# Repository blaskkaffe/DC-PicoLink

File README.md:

# DC-PicoLink

> **Part of the DC- Dreamcast family** (branch `unified`): [DC-DreamDash](https://github.com/blaskkaffe/DC-DreamDash/tree/unified) · [DC-PicoLink](https://github.com/blaskkaffe/DC-PicoLink/tree/unified) · [DC-iBlueControlMod](https://github.com/blaskkaffe/DC-iBlueControlMod/tree/unified) · [DC-BlueRetro](https://github.com/blaskkaffe/DC-BlueRetro/tree/unified) · [DC-openMenu-Virtual-Folder-Bundle](https://github.com/blaskkaffe/DC-openMenu-Virtual-Folder-Bundle/tree/unified) · [DC-Pico2Maple](https://github.com/blaskkaffe/DC-Pico2Maple/tree/unified). They work alone and together. The shared plan, feature list, vocabulary and licenses overview are in [docs/unified/](docs/unified/README.md).

> ⚠️ **Under development. No guarantee that anything here works.**
> Use it at your own risk, on hardware you can afford to lose: wiring mistakes or firmware
> bugs can damage a Dreamcast, a modem or the boards. Tried on hardware: the RP2040 cable with
> DreamPi, and the **RP2040-Zero + ESP32-S3 SuperMini stack** on a breadboard (the boards joined
> by wires) over the serial cable: Wi-Fi, PPP, DNS, VPN, UPnP, DCNow!; Quake, Quake III, Unreal
> Tournament, Alien Front Online. Written and host-tested but **not tried on hardware yet**: the
> soldered stack, the SD slot and its files over Wi-Fi, W5500 emulation through the ESP32, the
> BBA port, the USB modem, DCNet, Netlink. Expect bugs; the checklist is
> [docs/TESTING.md](docs/TESTING.md). When you report a problem, include the first status line
> (firmware version) and the log.

An RP2040-based Dreamcast serial-port adapter: a full coder's cable (serial and serial
PPP), W5500 Ethernet emulation over USB networking, and SD card emulation (used by
openMenu for its settings and VMU backups). Works with DreamPi or a regular computer,
as a cheaper, faster alternative to separate coder's cables and W5500 adapters, and (being
built) with an ESP32-S3 instead of a computer: [hardware/ESP32.md](hardware/ESP32.md), [esp32/](esp32).

One small board on the Dreamcast's serial port shows up on the computer as one USB
device with three functions. It works out by itself which one the Dreamcast is using:

| The Dreamcast thinks it has… | Used for | On the computer |
|---|---|---|
| a **coder's cable** (UART) | dc-tool-ser / dcload-serial, the KOS console, serial PPP games (e.g. AFO through DreamPi's Netlink) | a USB serial port (`/dev/dccable` on DreamPi) |
| a **WIZnet W5500** Ethernet chip | KallistiOS homebrew and patched games with the W5500 driver | a USB network interface (`dcusb0`) the computer routes or bridges |
| an **SD card** | openMenu (settings, per-game VMU backups), other SCIF-SPI SD programs | a disk image on the host (DreamPi), or a microSD in the board's own slot (written, not tried on hardware); with the ESP32, the slot card's files over Wi-Fi |

## Status

Working on hardware with DreamPi (Raspberry Pi, Linux):

* Serial: dc-tool-ser / dcload-serial 1.0.6 uploads clean at 115200 and 1.5 Mbaud
  (1.6 Mbaud is above what the Dreamcast's SCIF can do), the KOS console, Netlink serial
  PPP. Exact Dreamcast baud rates and auto-baud. No flow control from the Dreamcast, as
  DreamPi 2.1 (games and current KallistiOS leave its RTS floating, and waiting for it
  blocked the cable: DEVLOG, Nov 2026).
* W5500: KOS networking, DreamKarts and RuneScape online, JaderFox tester, ping, Quake 3
  server list and play (with `dcusb0-masterfix`).
* Being tested: AFO over serial (drops while fetching game info), Quake 3 map images over
  serial, Unreal Tournament (needs its server's address), Dreamcast Now! for W5500.
* SD card: works with KOS's SD driver; openMenu 1.7.1 doesn't find the card yet.

On a DreamPi the W5500 Dreamcast is meant to look exactly like DreamPi's modem Dreamcast
(DreamPi is the reference; its behaviour is written down in the project's DreamPi spec):

| | DreamPi add-on (`host/dreampi`) |
|---|---|
| Dreamcast Live VPN address (T+1) | `dcusb0-vpn` |
| Own LAN address (DreamPi's, e.g. .98): Internet traffic, router port forwards | `LAN_ALIAS=auto` |
| DreamPi's DNS (community DNS + DreamPi's overrides) | `DNS=auto` |
| TTL 64, PowerSmash double-SYN filter | `dcusb0-vpn` / DreamPi's own rule |
| DreamPi's game packet helpers (dcgamespy, dc2k2, dcvoip, dcdaytona) | fed / kept correct for `dcusb0` |
| Dreamcast Now! "online" | `dcusb0-dcnow` |
| Quake 3 server list (master ignores the word `dreamcast`) | `dcusb0-masterfix` (ours) |

The ESP32 (no computer) applies the same rules itself; what is still missing is listed in
[hardware/ESP32.md](hardware/ESP32.md) and the project's DreamPi spec. Tried over the serial cable
on a breadboard build (see the warning at the top).

Other hosts (Linux PC, macOS, Windows, Android) are planned: see [docs/ROADMAP.md](docs/ROADMAP.md).

## The stack: RP2040-Zero + ESP32-S3 SuperMini (no computer needed)

Tried on a breadboard build over the serial cable; the soldered stack is next. The two boards
sit back to back; the RP2040 does everything towards the Dreamcast, the ESP32 the Internet
side. Pinout: [Wiring](#wiring-full-pinout) below, details in [hardware/ESP32.md](hardware/ESP32.md);
ESP32 details: [esp32/README.md](esp32/README.md).

| | What it does | Like DreamPi |
|---|---|---|
| Internet | home Wi-Fi, or a W5500 Ethernet module on the ESP32 as uplink | |
| Setup | own Wi-Fi network `DC-PicoLink-XXXX`, web page with status, log, settings | |
| Serial cable | modem emulation (`AT`, `ATD`), PPP server, NAT | serial PPP |
| W5500 emulation | the Dreamcast's W5500 network: DHCP, DNS, NAT | `dcusb0` |
| SD card | a microSD on the Zero's SPI1 is the Dreamcast's SD card | (dcsd image) |
| SD files | the slot card's files on the web page: copy saves to and from a computer or phone | |
| USB modem | a USB voice modem on the ESP32: dial tone, number, answer, PPP | yes |
| BBA | the Dreamcast's Broadband Adapter on the ESP32's W5500 module | |
| DNS | DreamPi's DNS list from dreamcast.online, revival DNS; over TCP when the router intercepts DNS | yes |
| DCNow! | reports, and `dreampi.local:1998` for dreamcast.online/now/configure | yes |
| Network switch | two buttons at the top of the page: DCNow! (default) or DCNet, from the next call, whatever number the game dials; `*69` still goes to DCNet while DCNow! is selected (tick box). Also `call net.select dcnow\|dcnet` in the DC API (`POST /dcapi`), `POST /dcnow`, `/dcnet`, `GET /tag`, `/openmenu/poll` | yes |
| Wi-Fi from the console | `call wifi.scan`, `get wifi.scan.*`, `set wifi.pass ...`, `call wifi.join <name or #n>` in the DC API, and the page's Search button (list, filter, tap to pick) | |
| DCNet | `*69` before the number, or every call (the switch) | yes |
| Netlink | direct dial, matchmaking, game server codes, XBAND, Capcom matching (USB modem) | yes |
| VPN | Dreamcast Live, profiles built in (okayed by Dreamcast Live); the Dreamcast gets its own VPN address; auto mode pings every server and takes the fastest | yes |
| Own home address | as DreamPi: the Dreamcast gets .98 on your network (this box .99, answers ARP for it, no NAT); 1:1 with the VPN up | yes |
| Port forwarding | DreamPi's game ports by UPnP straight to the Dreamcast's .98, nothing else; says when the provider shares your IPv4 (then the VPN is switched on) | yes (optional there) |
| Game packet rules | TTL 64, PowerSmash double SYN, Planet Ring / Daytona public address, DNAT address swaps (dnat.txt) | yes |
| Serial line queue | game (UDP) packets go ahead of downloads on the slow serial line | |
| Updates | both boards from the web page (ESP32 image; the Zero restarts into its USB drive) | |

Test before trusting it: [docs/TESTING.md](docs/TESTING.md).

## Wiring (full pinout)

The stack: an RP2040-Zero and an ESP32-S3 SuperMini, back to back. Every signal below is 3.3 V
logic. The older single-board layouts (a Pico or Pro Micro with the Dreamcast on GPIO2-7, a UART
link to the ESP32) are only for testing: [hardware/WIRING.md](hardware/WIRING.md). More detail:
[hardware/ESP32.md](hardware/ESP32.md), [hardware/SD-SLOT.md](hardware/SD-SLOT.md).

### Dreamcast side

The usual way in is a **DC SD Adapter V2** in the serial port with an SD extender / sniffer
board in its slot (the adapter only maps the port's pins to SD contacts). An internal install
solders the same signals to the serial port's pins. Names are the Dreamcast's own (its TXD is
what it sends).

| Dreamcast signal | Serial port pin | SD contact: full-size / microSD | RP2040-Zero | Needed for |
|---|---|---|---|---|
| TXD (SPI MOSI) | 5 | 2 CMD / 3 | GP10 | serial, W5500, SD |
| RXD (SPI MISO) | 4 | 7 DAT0 / 7 | GP11 | serial, W5500, SD |
| RTS (SPI CS) | 6 | 1 DAT3 / 2 | GP12 | W5500, SD (serial only reads it) |
| CTS (SPI clock) | 7 | 5 CLK / 5 | GP9 | W5500, SD (the cable reads the line) |
| CTS drive | – | – | GP13 **→ 1 kΩ →** GP9 | serial flow control; a resistor on the board, no wire to the Dreamcast |
| GND | 3, 8 | 3 + 6 VSS / 6 | GND | everything |
| 3.3 V sense (optional) | 10 | 4 VDD / 4 | GP29 **via 10 kΩ** (about 10 kΩ; 9.1 kΩ is fine) | knowing when the Dreamcast is on; never to the board's 3V3 |
| +5 V | 1 | – | not connected | see [Power](#power-and-usb) |

**Which wires are needed.** Serial alone works with TXD, RXD and GND. W5500 and the SD card use
all four signal wires (TXD, RXD, RTS, CTS), because there they are the SPI bus: so with all three
functions, wire all four. CTS is one pin on the Dreamcast that does two jobs. In serial mode it is
an input: the cable pulls it high through GP13 to say "stop sending" when its buffer is nearly
full. In W5500/SD mode the Dreamcast turns it into the SPI clock, an output. GP9 reads what is
really on the line (which is also how the cable notices SPI mode), and the 1 kΩ lets both sides
drive it without harm ([why](hardware/WIRING.md#why-the-1-kω-resistor)). Without the GP13
resistor serial still works, but the cable can no longer slow the Dreamcast down. The sense wire
is optional: without it the cable decides the Dreamcast is on when it sees TXD or RTS high.
Serial port pins 2 and 9 and SD contacts 8 and 9 (DAT1, DAT2) stay unconnected. The pin numbers come from coder's
cable guides: measure before soldering.

### The stack: which pins are joined

RP2040-Zero on top, face up; ESP32-S3 SuperMini underneath, face down; both USB sockets at
the same end; positions count from the USB end. **Solder only what the table says**, and put
insulation (Kapton) between the two boards' backs.

| Pos | Zero left ↔ SuperMini | | Zero right ↔ SuperMini | |
|---|---|---|---|---|
| 1 | 5V ↔ 5V | **solder** | GP0 ↔ GPIO43 | optional (ESP32 console TX) |
| 2 | GND ↔ GND | **solder** | GP1 ↔ GPIO44 | optional (ESP32 console RX) |
| 3 | 3V3 ↔ 3V3 | **never** (two regulators) | GP2 ↔ GPIO1 | not used (optional, strength) |
| 4 | GP29 ↔ GPIO13 | **never** (GP29 is the power sense / W5500 MISO) | GP3 ↔ GPIO2 | **solder**: HS (ESP32 ready) |
| 5 | GP28 ↔ GPIO12 | **never** (SD MISO / W5500 SCLK) | GP4 ↔ GPIO3 | **solder**: SPI MISO (ESP32 → Zero) |
| 6 | GP27 ↔ GPIO11 | **never** (GP27 free / W5500 MOSI) | GP5 ↔ GPIO4 | **solder**: SPI CS |
| 7 | GP26 ↔ GPIO10 | **never** (SD SCK / W5500 CS) | GP6 ↔ GPIO5 | **solder**: SPI clock |
| 8 | GP15 ↔ GPIO9 | **never** (SD MOSI / W5500 INT) | GP7 ↔ GPIO6 | **solder**: SPI MOSI (Zero → ESP32) |
| 9 | GP14 ↔ GPIO8 | **never** (GP14 is the SD card's CS) | GP8 ↔ GPIO7 | **solder**: DR (ESP32 has data) |

Left 4-9 are the Zero's power sense (GP29), SD slot pins (GP28, GP26, GP15, GP14) and the free GP27 over the ESP32's W5500 pins (GPIO9-13):
all used, each from the outside (the Zero's edge pads, the SuperMini's holes from its outer face), none joined.
The same pin map serves the stripboard layout ([hardware/STRIPBOARD.md](hardware/STRIPBOARD.md); a PCB with an SD-card plug: [hardware/stack-pcb](hardware/stack-pcb/README.md)): there the boards stand side by side. The Zero's bottom
edge GP9-13 is the Dreamcast (table above). GP16 is the Zero's own RGB LED (red: no ESP32,
yellow: damaged link packets, green: link up, blue: link up and the Dreamcast on).

### SD card slot (optional)

A 3.3 V microSD module or breakout on the RP2040-Zero's SPI1, never on the Dreamcast's wires.

| SD module | RP2040-Zero |
|---|---|
| CLK / SCK | GP26 |
| CMD / DI / MOSI | GP15 (Pico layout: GP27) |
| DAT0 / DO / MISO | GP28 |
| DAT3 / CS | GP14 |
| VCC / GND | 3V3 or 5V, see [SD-SLOT.md](hardware/SD-SLOT.md#which-vcc) / GND |

No card-detect pin: the cable looks for a card every 2 s.

### ESP32-S3 extras (optional)

| ESP32-S3 SuperMini | Connects to |
|---|---|
| GPIO12 | W5500 module SCLK |
| GPIO11 | W5500 module MOSI |
| GPIO13 | W5500 module MISO |
| GPIO10 | W5500 module CS (SCS) |
| GPIO9 | W5500 module INT |
| 3V3, GND | W5500 module 3.3 V, GND |
| USB-C (modem build) | a USB host for one device (a hub works too): a USB voice modem through an OTG adapter (the Dreamcast's modem joins it by a phone cord, as with a DreamPi), or a DC-PicoLink cable: the link then runs over USB, no link wires needed |
| GPIO43 / GPIO44 | console TX / RX (UART0, 115200) |

The W5500 module is the Internet uplink when a router answers DHCP on it, otherwise the
socket for the Dreamcast's Broadband Adapter.

### Power and USB

* **Today:** 5V and GND are joined, so either board's USB powers both. **Plug in one USB at a
  time** (the Zero has no diode on its USB 5 V). The Zero's USB is for updates and for a
  computer (it then takes the serial and network traffic, as with DreamPi); the ESP32's USB-C
  is its console, or in the modem build the socket for a USB modem, a USB Ethernet adapter or a
  DC-PicoLink cable (then the link runs over USB and needs no link wires; the ESP32 powers it).
* **From the Dreamcast (serial port pin 1, +5 V):** not measured yet, so not recommended. Any
  such feed goes through a Schottky diode (e.g. SS14) so a USB cable plugged in later can't push
  power back into the console. Current budget and options: [hardware/ESP32.md](hardware/ESP32.md#power).
* Never join the Dreamcast's 3.3 V (port pin 10 / SD VDD) to a board's 3V3: it goes only to the
  sense pin, through 10 kΩ.

## IP plan

The same Dreamcast settings work on the ESP32 box and on a DreamPi with this add-on. 98: the
Dreamcast's launch year in Japan, and its usual last number on the home network.

| Network | The box (or Pi) | The Dreamcast |
|---|---|---|
| Setup Wi-Fi `DC-PicoLink-XXXX` (ESP32) | 192.168.4.1: the web page (also `http://dreampi.local`) | – |
| **The Dreamcast network**: the W5500 (cable), the BBA socket (W5500 module), a PPP call without its home address | 192.168.98.1: gateway and DNS | DHCP .2–.99 (a PPP call gets .2); a fixed address at **.100** or above, mask 255.255.255.0, gateway and DNS 192.168.98.1 |
| Modem / serial PPP with its home address (default) | home network, usually .99 | home network, usually .98 (no NAT; port forwarding points there). Picked as DreamPi does: counting down from .99, the first free address is the box's end of the link, the next the Dreamcast's |
| VPN (Dreamcast Live) | the address the server gives | that address + 1 (only the server's game networks go through the tunnel) |
| DreamPi's W5500 network (`dcusb0`) | 192.168.98.1 | DHCP .10–.50, fixed .100 or above |

The Dreamcast uses one way to connect at a time, so they share one network: the box answers on
the interface the Dreamcast was last heard on. On the W5500, gateway and DNS must be set to
192.168.98.1 (0.0.0.0 only works over the modem, where PPP fills them in).

Which address where (the ESP32 box):

| Dreamcast joined by | Internet over | The Dreamcast gets |
|---|---|---|
| The cable's emulated W5500 (RP2040) | Wi-Fi or the wired uplink | 192.168.98.x (DHCP), NAT to the uplink |
| BBA into the W5500 module (BBA role) | Wi-Fi only: the module's one port is the Dreamcast's | 192.168.98.x (DHCP), NAT to Wi-Fi |
| Modem (USB) or the cable's serial port | Wi-Fi or the wired uplink | home network .98 (or 192.168.98.2 when no home address is free) |

The W5500 module picks its role by itself: if a router answers DHCP on its cable it is the way to
the Internet (the router's address, ahead of Wi-Fi), if nothing answers in 10 s it is the BBA
socket. A USB Ethernet adapter is not supported yet.

## Quick start (DreamPi)

1. **Wire it** to the Dreamcast serial port: [hardware/WIRING.md](hardware/WIRING.md)
   (SD-adapter plug build; an internal install works the same way).
2. **Flash** a Raspberry Pi Pico: hold BOOTSEL, plug in, copy
   `dc-picolink-<version>-250mhz.uf2` from the [releases](../../releases).
3. **Install the DreamPi side**: copy `dc-picolink-dreampi-setup.sh` to the Pi and run
   `sudo bash dc-picolink-dreampi-setup.sh`.
4. **Serial PPP** (Netlink): in DreamPi's `netlink_config.ini` set `port = /dev/dccable`.
5. **W5500**: the Dreamcast gets an address by DHCP (192.168.98.x). Static settings:
   IP 192.168.98.100, mask 255.255.255.0, gateway 192.168.98.1, DNS 192.168.98.1 (DreamPi's DNS;
   46.101.91.123 without DreamPi). Settings: `/etc/dcusb0.conf` (an untouched 192.168.99.x one from
   an older version is replaced by the installer with 192.168.98.x).
6. **Check**: `sudo dreampi-snapshot` prints what the DreamPi and the add-on are doing.

Logs: `journalctl -fu dcsd` (the cable's own status lines), `journalctl -u dcusb0`,
`journalctl -u dcusb0-vpn`, `journalctl -u dcusb0-dcnow`, `journalctl -u dcusb0-masterfix`.

dcload test: build dc-tool-ser on the Pi (KallistiOS `dcload-serial`, `make -C host-src/tool`),
boot a dcload-serial CDI, then `dc-tool-ser -t /dev/dccable -b 1500000 -x program.elf`.

## Repository

| Folder | |
|---|---|
| [`firmware/`](firmware) | RP2040 firmware (Pico SDK, PIO) and its host-side tests (`firmware/tests`) |
| [`host/`](host) | software for the computer side: `dreampi/` today; `linux/`, `macos/`, `windows/` planned |
| [`esp32/`](esp32) | ESP32-S3 firmware: the cable's link to Wi-Fi without a computer (under test) |
| [`hardware/`](hardware) | wiring and build notes, [SD slot](hardware/SD-SLOT.md), [ESP32](hardware/ESP32.md) |
| [`docs/`](docs) | [architecture](docs/ARCHITECTURE.md), [technical reference](docs/REFERENCE.md), [roadmap](docs/ROADMAP.md), [testing](docs/TESTING.md), [development log](docs/DEVLOG.md) |
| [`tools/`](tools) | test runner (`run-tests.sh`) and the scripts it calls, DreamPi installer builder, `dctest/` (Dreamcast test program and host tool), network-namespace tests of the DreamPi add-on, `dreampi_vpn_extract.py` (VPN profiles out of a DreamPi image, plain Python, works in a-Shell on iOS) |

## Building

Cable (RP2040), Pico SDK 2.1.1 and `gcc-arm-none-eabi`:

```sh
# Test layout, single Pico / Pro Micro (Dreamcast on GPIO2-7, ESP32 link on UART GPIO12-15)
cmake -S firmware -B build -DPICO_BOARD=pico -DDC_SYS_KHZ=250000 && make -C build
# The stack: RP2040-Zero + ESP32-S3 SuperMini (Dreamcast on GP9-14, ESP32 link over SPI)
cmake -S firmware -B build-zero -DPICO_BOARD=pico -DDC_SYS_KHZ=250000 -DDC_BOARD=zero-stack && make -C build-zero
```

The UF2 is `build*/dc_usb_serial.uf2`: hold BOOT (BOOTSEL), plug in, copy it to the drive.
`-DPICO_BOARD=pico` is right for the RP2040-Zero and Pro Micro too (generic 2 MB flash).

ESP32-S3, ESP-IDF 5.4 (details in [esp32/README.md](esp32/README.md)):

```sh
cd esp32
idf.py set-target esp32s3 && idf.py build                                             # UART link (test layout)
idf.py -B build-zero -D SDKCONFIG=build-zero/sdkconfig \
       -D SDKCONFIG_DEFAULTS="sdkconfig.defaults;sdkconfig.zero-stack" build          # SPI link (stack)
idf.py -B build-modem -D SDKCONFIG=build-modem/sdkconfig \
       -D SDKCONFIG_DEFAULTS="sdkconfig.defaults;sdkconfig.zero-stack;sdkconfig.modem" build   # + USB modem port
```

Tests (host, no hardware): `tools/run-tests.sh` runs the C model tests, including the SPI
link's timing simulation; `tools/run-tests.sh build` adds the PIO simulations for both
Dreamcast pin layouts. More options: [docs/REFERENCE.md#build](docs/REFERENCE.md#build).
CI builds every push; tagged versions (`v*`) become releases with the UF2 files and the
DreamPi installer.

Part of a family of `DC-` Dreamcast projects.

`esp32/probe` is a test firmware for one question: can the ESP32-S3 do the RP2040's job too?
Measured: no (Wi-Fi pauses the other core for ~40 ns). See [hardware/ESP32-ONLY.md](hardware/ESP32-ONLY.md).

## Credits and licenses

MIT, see [LICENSE](LICENSE). Built on the work of others:

* [DreamPi](https://github.com/Kazade/dreampi) (Kazade and contributors, MIT): the reference for
  everything the ESP32 does for a modem Dreamcast.
* [Netlink](https://github.com/eaudunord/Netlink) (eaudunord): the Netlink tunnel ported to
  `esp32/main/netlink.c`.
* DCNet by flyinghead (`dcnet.rpi`, as used by DreamPi): the access-point protocol in `dcnet.c`.
* Dreamcast Live (Shuouma): the VPN servers and the client profiles in `esp32/vpn/`, used here
  with their okay.
* Espressif `mdns` and `usb_host_cdc_acm` components (Apache-2.0), vendored in `esp32/components/`.
* **Raspberry Pi Pico SDK 2.1.1** (BSD-3-Clause, Raspberry Pi (Trading) Ltd) and its **TinyUSB** (MIT): the
  firmware is built against them, not copied; `firmware/pico_sdk_import.cmake` is the SDK's own file and keeps its header.
* **KallistiOS**: the Dreamcast test program `tools/dctest` is built against it in CI (fetched at build time;
  BSD-style license, see its repository).

The documents in [docs/unified/](docs/unified/README.md) are covered by the same MIT license. For the licenses of
the other repositories in the family see the table there.

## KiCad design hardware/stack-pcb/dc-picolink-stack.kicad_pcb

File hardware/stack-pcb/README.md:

# Stack PCB: RP2040-Zero + ESP32-S3 SuperMini with an SD-card plug

> ⚠️ Not made or tested yet. Routed and checked with KiCad's DRC (0 errors, 0 unconnected). Check the
> points under **Before ordering** against your own parts first.

The middle board of a 3-board stack ([../ESP32.md](../ESP32.md#the-rp2040-zero--esp32-s3-supermini-stack-spi-link)):
the RP2040-Zero on its top face, the ESP32-S3 SuperMini on its bottom face, joined by long pins.
Its far end is shaped like a full-size SD card and goes into the slot of the DC SD adapter, so the
stack plugs straight into the Dreamcast's serial port. 18 mm wide (the modules' width), 24 mm at the
card end (an SD card's width: the slot needs it), 69.5 mm long.

On the board:

* **SD card end**: the Dreamcast lines on the card's contacts, wired as the DC SD adapter does
  (SPI over the serial port: TXD = MOSI, RXD = MISO, RTS = CS, CTS = SCK; [../WIRING.md](../WIRING.md)):
  contact 1 (CS) GP12 = DC RTS, 2 (CMD) GP10 = DC TXD, 3 and 6 GND, 4 the Dreamcast's 3.3 V,
  5 (CLK) GP9 = DC CTS, 7 (DAT0) GP11 = DC RXD.
* **Ribbon-cable row** (7 holes, 2.54 mm) right behind it, with the same signals: RXD, CTS, 3V3, GND,
  5V, TXD, RTS (power together, ground between the two supplies; the Dreamcast serial pin numbers
  4, 7, 10, 3, 1, 5, 6 are printed on the back).
  The card end is wired straight into these holes on the contact face (one via, for the second
  ground contact), so it can be **cut off along the printed line**
  and the stack wired to a serial plug with a ribbon cable instead.
* **5 V in**: ribbon hole 5, through D1 into the stack's 5V. The SD slot has no 5 V (its
  3.3 V is the Dreamcast's, sized for an SD card, and is only used for sensing here): power the stack
  through this hole (the Dreamcast's serial pin 1, or a charger) or a USB port. See [../ESP32.md#power](../ESP32.md#power).
* **W5500 row** (6 holes, under the ribbon row): CS, SCK, MISO, GND, 5V, MOSI for a W5500 Ethernet
  module on six jumper wires. The common blue module (2×5 header) has its own 3.3 V regulator and is
  fed from 5V; its 3V3, RST and INT pins stay free. The four signals come from ESP32 pins that reach
  this board where the Zero has nothing: IO43 (CS), IO44 (MISO), IO1 (SCK), IO11 (MOSI). The ESP32
  firmware for this board: add `sdkconfig.stack-pcb` (with the modem build also
  `sdkconfig.stack-pcb-modem`, which turns the serial console off: the W5500 has its pins; the log is
  on the web page as always).
* R1 1 kΩ GP13 → GP9 (flow control), R2 10 kΩ GP29 → the Dreamcast's 3.3 V (power sense).
* **microSD socket** for the slot card ([../SD-SLOT.md](../SD-SLOT.md): GP26 SCK, GP15 MOSI, GP28 MISO,
  GP14 CS) between the card end and the stack, on the ESP32's face, the card going in from the right
  edge seen from the blue (ESP32) side, which faces up (away from both USB ports). With 10 µF + 100 nF and 10 kΩ pull-ups on CS, MOSI, MISO, DAT1 and DAT2.

Same pin map and firmware as the soldered stack: cable `-DDC_BOARD=zero-stack`, ESP32 `sdkconfig.zero-stack`.

## Parts

| Ref | Part | Package | Face |
|---|---|---|---|
| J4 | **TF-01A** push-push microSD socket (Korean Hroparts, LCSC C91145, ~0.1-0.2 USD) | SMD | bottom |
| R3-R7 | 10 kΩ (card pull-ups) | 0805 | top |
| C1, C2 | 10 µF, 100 nF (card supply) | 0805 | top |
| R1 | 1 kΩ | 0805 | top |
| R2 | 10 kΩ | 0805 | top |
| D1 | B5819W (or SS14 in SOD-123F / any 1 A Schottky in SOD-123) | SOD-123 | top |
| – | long 2.54 mm pin headers (≥ 15 mm), 2 × 9 + 5 | | |
| – | optional: 7-pin 2.54 mm header for the ribbon cable, 6-pin for the W5500 | | |

Everything solders with an iron: the 0805 and SOD-123 parts use the hand-soldering pads, and the
socket's pins are 1.1 mm apart. Through-hole resistors and a DO-41 diode would not fit in the 18 mm
body without making the board longer.

The socket's land pattern is the one Bus Pirate 5 uses for the same part (checked against two other
open designs: they agree within 0.1 mm). Pins 1-8 are the microSD contacts in the usual order, pin 9
the card switch (not used).

## The stack pins

The Zero has 8 holes down each side and 7 along its bottom edge (GP8, GP9 … GP13, GP14): the corner
holes GP8 and GP14 are both the last side hole and the ends of the bottom row. The board has a hole
under each. The mark beside each hole (both faces) says how it is fitted:

* no mark: **one long pin through all three boards** (5V, GND; the six link pins GP3-GP8 ↔ ESP32 GPIO2-7);
* **z**: a pin from the Zero into this board only, **cut flush underneath** before the ESP32 goes on:
  3V3, GP29, GP28, GP26, GP15, GP14 and the bottom row GP9-GP13 (these must never reach the ESP32,
  see the table in ESP32.md);
* **e**: a pin from the ESP32 into this board only, **cut flush on top**; the Zero gets no pin there
  (its GP0, GP1, GP2 and GP27 are unused): IO43, IO44, IO1, IO11 for the W5500.

Every hole carries a signal, so none could be left out.

## Before ordering

* **SD contact positions**: they come from KiCad's SD socket footprints (two makers agree), not
  from a measured card. Print the board 1:1 and lay an SD card on it: the seven gold contacts
  must sit on the seven pads.
* **Your adapter's wiring**: the pin mapping is the standard one for these adapters (the jj1odm
  design that KallistiOS and DreamShell expect), and your own serial plug's labels match it. To be
  certain, check with a multimeter between the adapter's serial plug and its slot: CTS → card
  contact 5, TXD → 2, RXD → 7, RTS → 1, 3.3 V → 4, GND → 3 and 6.
* **Which way up**: the contacts are on the ESP32's face (the blue side in the pictures), which faces
  up in the adapter: the ESP32 is on top and the Zero underneath. The Zero then hangs about
  7 mm below the card (2.5 mm spacer + board + its USB-C socket): check the gap to the table.
  The power plug sits right above the adapter, and the stack starts where the card leaves the slot.
* **Card end length**: 22 mm, for an adapter that takes ~20 mm of the card (about 12 mm of a card
  sticking out, as in the photo). If more of your card goes in, raise `CARD` in `gen_board.py`.
* **Board**: 1.6 mm, **ENIG** (gold) finish: the contacts rub on the slot's springs. An SD card is
  2.1 mm thick. If the board is loose in the slot, a strip of Kapton on the top face of the card
  end takes up the play.
* The hole positions assume the Zero's and the SuperMini's first pin about 1.3 mm from the USB end,
  as in ESP32.md. Check with calipers.

## Assembly

1. SMD parts: the microSD socket on the bottom, the resistors, capacitors and D1 on top (D1's band
   toward the stack).
2. The four **e** holes first: a pin from below in each (header plastic underneath, like the ESP32's
   other pins), soldered on top and cut flush there.
3. Zero on top, face up, USB at the square end. Long pins through all its holes except the **e** ones;
   solder the top joints.
4. Cut the **z** pins flush underneath (the bottom row too). Kapton on the ESP32's back is a good idea
   (the board's tracks run under it). ESP32 face down onto the long pins and the **e** pins, USB at the
   same end; solder.
5. Before power: with a meter, check that the Zero's 3V3 and the ESP32's 3V3 are **not** joined,
   and that SD contact 4 does not touch either 3V3.

## Files

* `gen_board.py`: the whole board as a script (outline, parts, nets, labels): edit here.
* `make.sh`: generate → autoroute (Freerouting 1.9) → DRC → Gerbers, drill, pictures. Needs KiCad 7,
  Java and Xvfb: `FREEROUTING=/path/freerouting-1.9.0.jar ./make.sh build`. The router's result
  differs a little from run to run; the script stops if anything gets routed on the card end.
* `ses_import.py`: puts Freerouting's routes onto the board (pcbnew's own import needs the GUI).
* `dc-picolink-stack.kicad_pcb` / `.kicad_pro`: the routed board (KiCad 7+). No schematic: the nets
  are in `gen_board.py`.

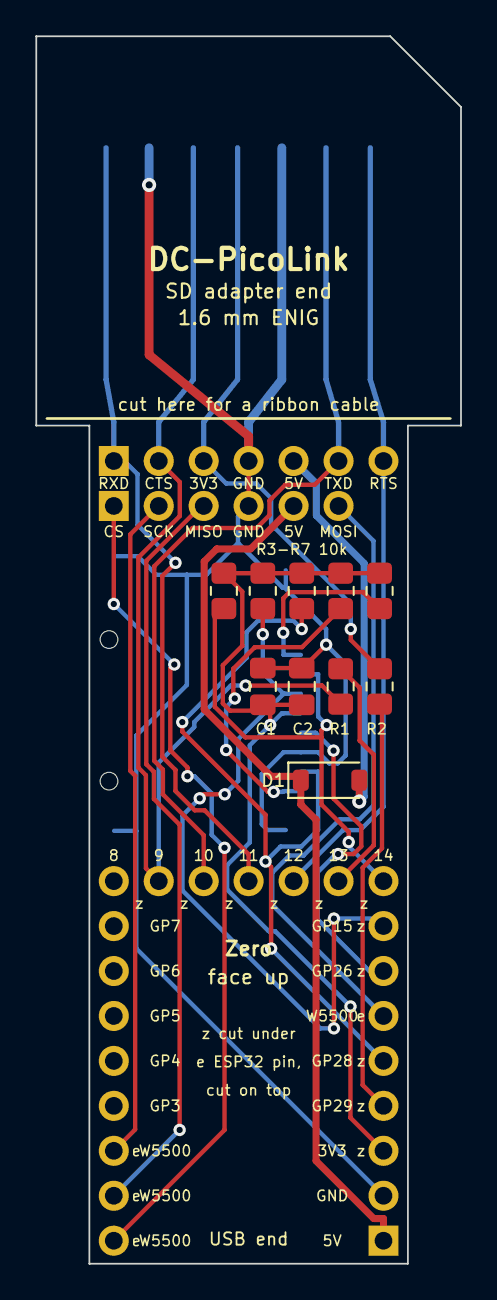
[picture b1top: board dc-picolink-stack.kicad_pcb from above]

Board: 2 copper layers, 24.0 x 69.4 mm, 15 parts (0 on the bottom side), 21 nets.

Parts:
C1: 10uF; C_0805_2012Metric_Pad1.18x1.45mm_HandSolder
C2: 100nF; C_0805_2012Metric_Pad1.18x1.45mm_HandSolder
D1: B5819W; D_SOD-123
J1: Stack: RP2040-Zero above, ESP32-S3 SuperMini below
J2: SD card edge to the DC SD adapter
J4: TF-01A microSD (LCSC C91145)
J5: Dreamcast serial: ribbon cable / 5 V in
J6: W5500 module (jumper wires)
R1: 1k; R_0805_2012Metric_Pad1.20x1.40mm_HandSolder
R2, R3, R4, R5, R6, R7: 10k; R_0805_2012Metric_Pad1.20x1.40mm_HandSolder

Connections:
+3V3: C1.1, C2.1, J1.R3, J4.4, R3.2, R4.2, R5.2, R6.2, R7.2
+5V: D1.1, J1.R1, J6.5
DC_3V3: J2.4, J5.3, R2.2
GND: C1.2, C2.2, J1.R2, J2.3, J2.6, J4.6, J4.11, J5.4, J6.4
GP9: J1.GP9, J2.5, J5.2, R1.1
GP10: J1.GP10, J2.2, J5.6
GP11: J1.GP11, J2.7, J5.1
GP12: J1.GP12, J2.1, J5.7
GP13: J1.GP13, R1.2
GP14: J1.R9, J4.2, R3.1
GP15: J1.R8, J4.3, R4.1
GP26: J1.R7, J4.5
GP28: J1.R5, J4.7, R5.1
GP29: J1.R4, R2.1
SD_DAT1: J4.8, R6.1
SD_DAT2: J4.1, R7.1
VIN: D1.2, J5.5
W_CS: J1.L1, J6.1
W_MISO: J1.L2, J6.3
W_MOSI: J1.R6, J6.6
W_SCLK: J1.L3, J6.2

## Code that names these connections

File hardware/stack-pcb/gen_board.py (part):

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ZL = ["W_CS", "W_MISO", "W_SCLK", "GP3_HS", "GP4_MISO", "GP5_CS", "GP6_SCK", "GP7_MOSI", "GP8_DR"]
# The W5500 runs on four ESP32 pins that reach this board where the Zero has nothing: IO43 (CS),
# IO44 (MISO), IO1 (SCLK) under the Zero's unused GP0-GP2, IO11 (MOSI) under its unused GP27.
TOP_LABEL = {"W_CS": "W5500", "W_MISO": "W5500", "W_SCLK": "W5500", "W_MOSI": "W5500"}
BOT = ["GP9", "GP10", "GP11", "GP12", "GP13"]                 # x = XL + 1..5 pitches
# F = one long pin through all three boards, Z = Zero to this board only (cut flush underneath),
# E = ESP32 to this board only (cut flush on top; no Zero pin). The bottom row GP9-GP13 is all Z.
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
